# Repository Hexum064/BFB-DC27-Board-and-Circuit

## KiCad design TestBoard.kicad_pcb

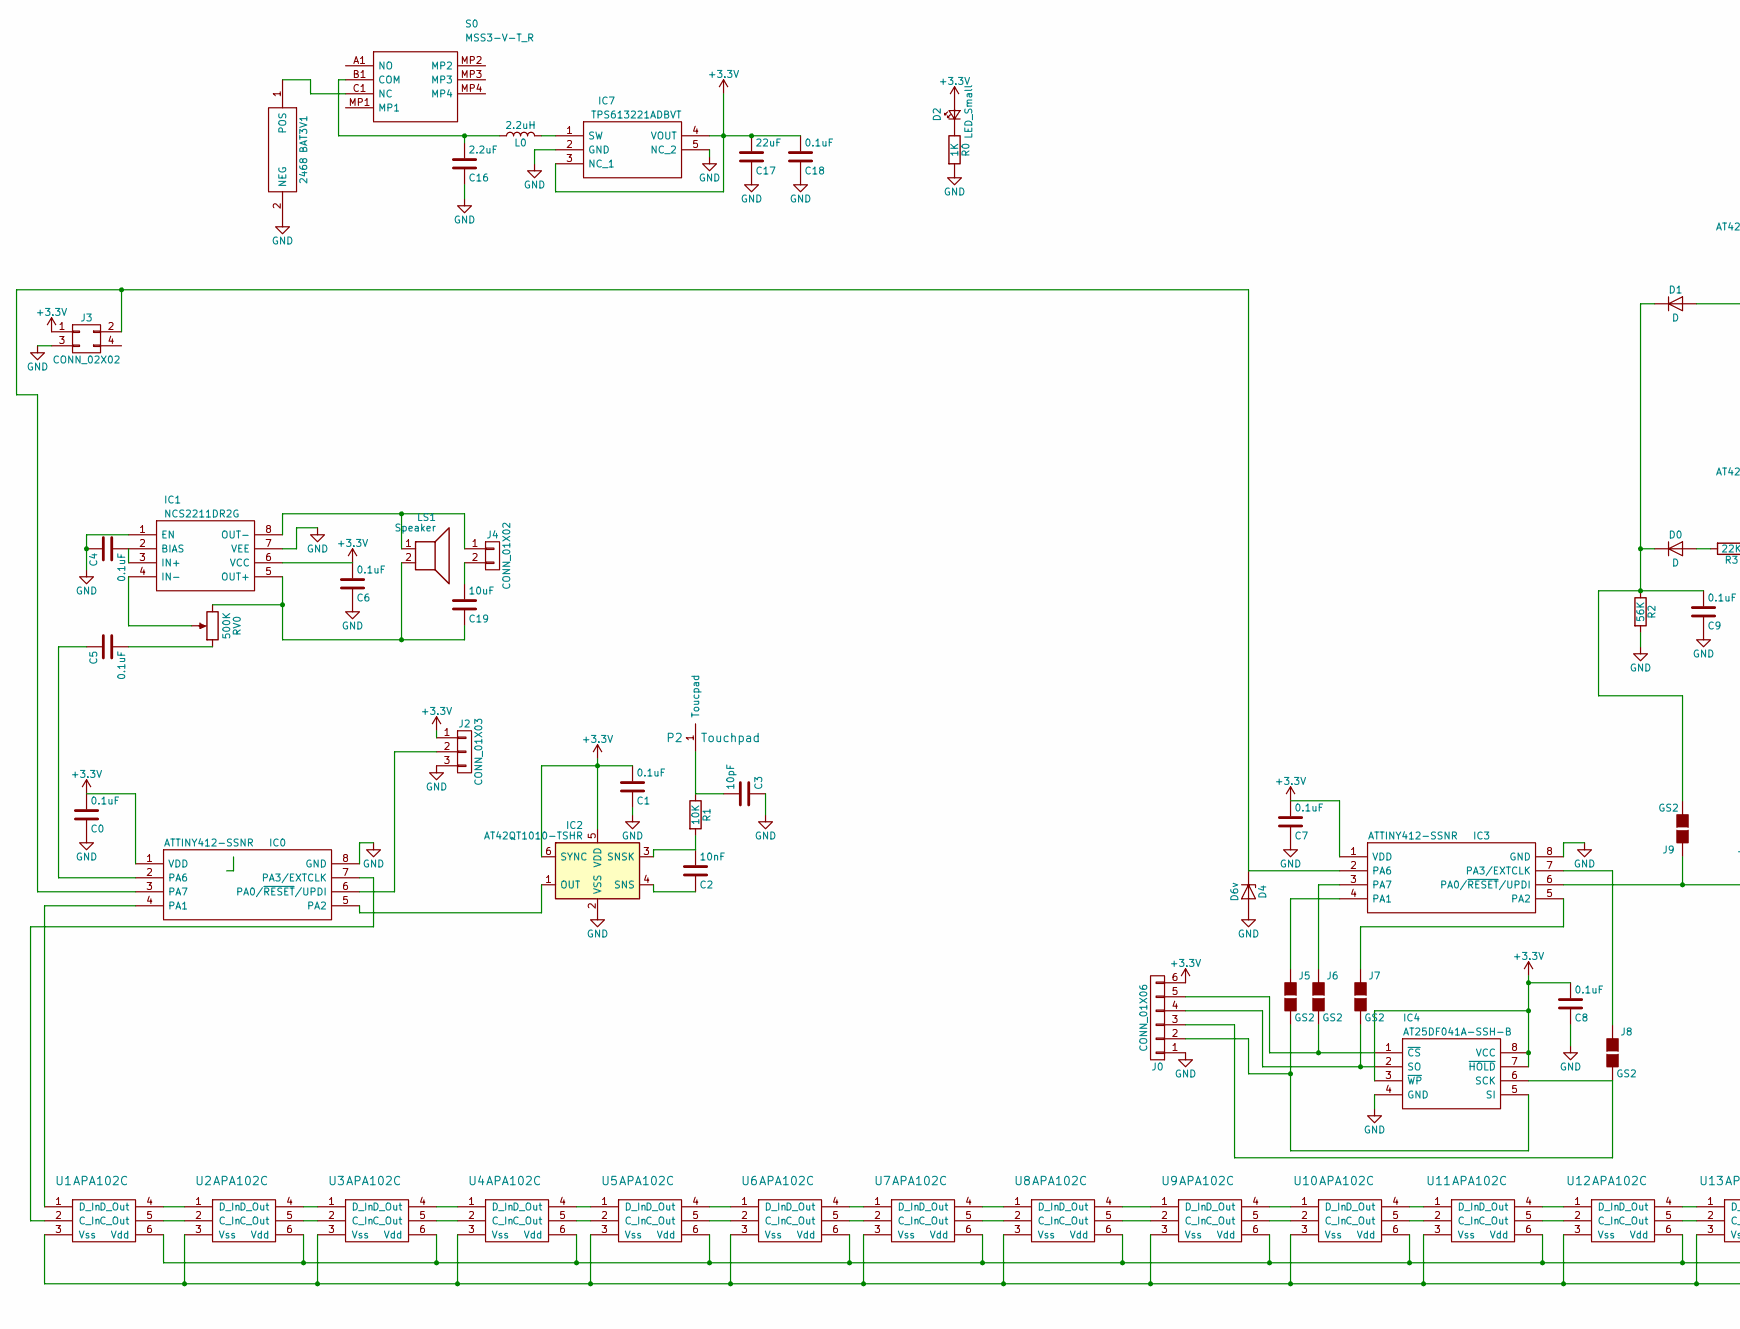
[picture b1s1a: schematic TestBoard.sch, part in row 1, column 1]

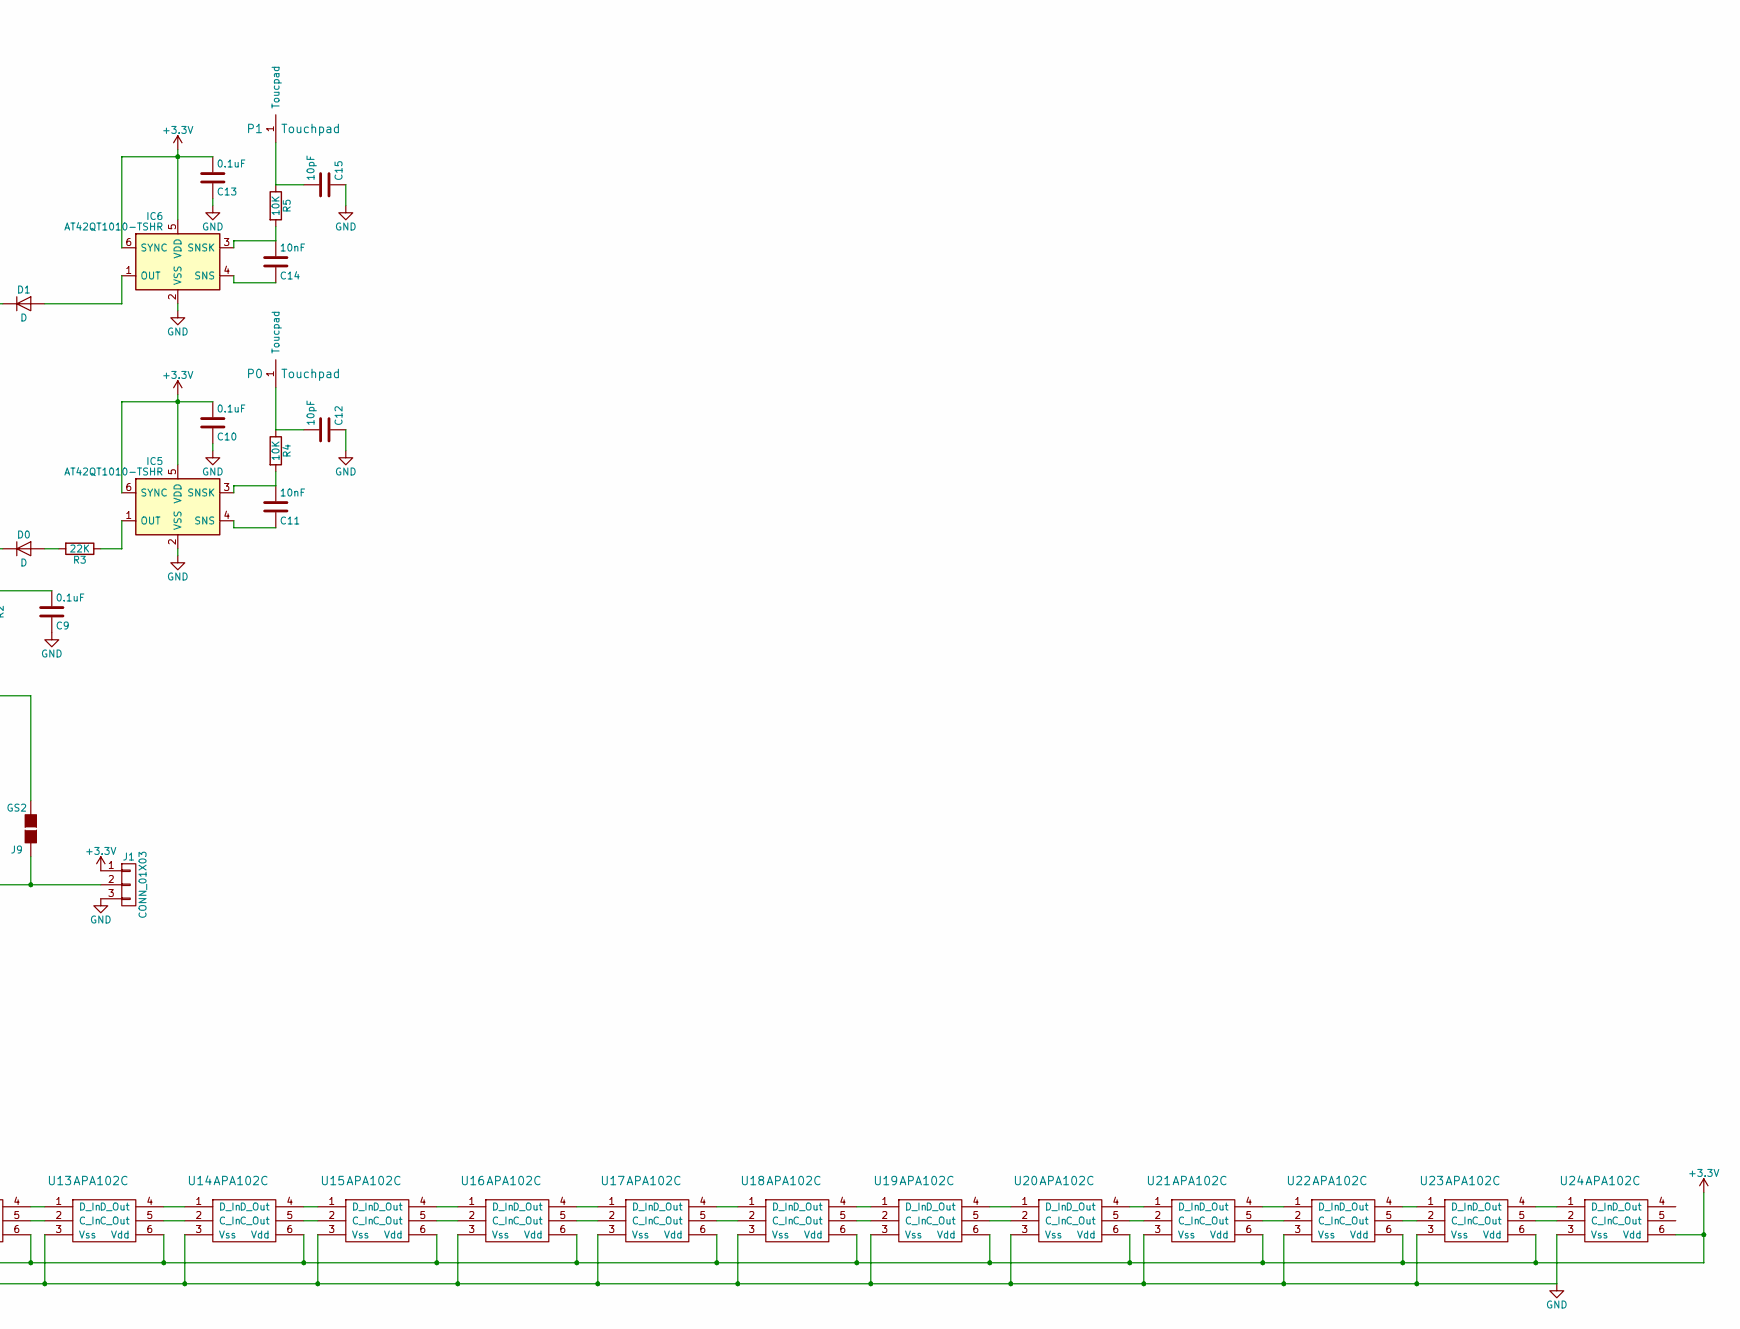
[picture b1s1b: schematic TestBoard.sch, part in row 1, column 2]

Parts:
BAT3V1: 2468; Manufacturer_Part_Number 2468; Mouser Part Number 534-2468
C0, C1, C4, C5, C6, C7, C8, C9, C10, C13, C18: 0.1uF; C_0603
C2, C11, C14: 10nF; C_0603
C3, C12, C15: 10pF; C_0603
C16: 2.2uF; C_0603
C17: 22uF; C_0603
C19: 10uF; C_0603
D0, D1: D; D_0603
D2: LED_Small; LED_0603
D4: D6v; D_0603
IC0, IC3: ATTINY412-SSNR; SOIC127P600X175-8N; Manufacturer_Part_Number ATTINY412-SSNR; Mouser Part Number 556-ATTINY412-SSNR
IC1: NCS2211DR2G; SOIC127P600X175-8N; Manufacturer_Part_Number NCS2211DR2G; Mouser Part Number 863-NCS2211DR2G
IC2, IC5, IC6: AT42QT1010-TSHR; SOT-23-6
IC4: AT25DF041A-SSH-B; SOIC127P600X175-8N; Manufacturer_Part_Number AT25DF041A-SSH-B
IC7: TPS613221ADBVT; SOT95P280X145-5N; Manufacturer_Part_Number TPS613221ADBVT; Mouser Part Number 595-TPS613221ADBVT
J0: CONN_01X06; Pin_Header_Straight_1x06_Pitch2.54mm
J1, J2: CONN_01X03; Pin_Header_Straight_1x03_Pitch2.54mm
J3: CONN_02X02; Pin_Header_Straight_2x02_Pitch2.54mm
J4: CONN_01X02; Pin_Header_Straight_1x02_Pitch2.54mm
J5, J6, J7, J8, J9: GS2
L0: 2.2uH; L_Neosid_SMS-ME3015
LS1: Speaker; Pin_Header_Straight_1x02_Pitch2.54mm
P0, P1, P2: Touchpad
R0: 1K; R_0603
R1, R4, R5: 10K; R_0603
R2: 56K; R_0603
R3: 22K; R_0603
RV0: 500K; Potentiometer_Trimmer_Vishay_TS53YJ
S0: MSS3-V-T_R; MSS3VTR; Manufacturer_Part_Number MSS3-V-T/R; Mouser Part Number 113-MSS3-V-T/R
U1, U2, U3, U4, U5, U6, U7, U8, U9, U10, U11, U12, U13, U14, U15, U16, U17, U18, U19, U20, U21, U22, U23, U24: APA102C; LED_RGB_5050-6

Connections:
+3V3: C0.2, C1.2, C6.2, C7.2, C8.2, C10.2, C13.2, C17.2, C18.2, D2.2 (A), IC0.1 (VDD), IC1.6 (VCC), IC2.5 (VDD), IC2.6 (SYNC), IC3.1 (VDD), IC4.3 (~WP), IC4.7 (~HOLD), IC4.8 (VCC), IC5.5 (VDD), IC5.6 (SYNC), IC6.5 (VDD), IC6.6 (SYNC), IC7.3 (NC_1), IC7.4 (VOUT), J0.6, J1.1, J2.1, J3.1, U1.6 (Vdd), U2.6 (Vdd), U3.6 (Vdd), U4.6 (Vdd), U5.6 (Vdd), U6.6 (Vdd), U7.6 (Vdd), U8.6 (Vdd), U9.6 (Vdd), U10.6 (Vdd), U11.6 (Vdd), U12.6 (Vdd), U13.6 (Vdd), U14.6 (Vdd), U15.6 (Vdd), U16.6 (Vdd), U17.6 (Vdd), U18.6 (Vdd), U19.6 (Vdd), U20.6 (Vdd), U21.6 (Vdd), U22.6 (Vdd), U23.6 (Vdd), U24.6 (Vdd)
GND: BAT3V1.2 (NEG), C0.1, C1.1, C3.1, C4.1, C6.1, C7.1, C8.1, C9.1, C10.1, C12.1, C13.1, C15.1, C16.1, C17.1, C18.1, D4.2 (A), IC0.8 (GND), IC1.1 (EN), IC1.7 (VEE), IC2.2 (VSS), IC3.8 (GND), IC4.4 (GND), IC5.2 (VSS), IC6.2 (VSS), IC7.2 (GND), IC7.5 (NC_2), J0.1, J1.3, J2.3, J3.3, R0.2, R2.2, U1.3 (Vss), U2.3 (Vss), U3.3 (Vss), U4.3 (Vss), U5.3 (Vss), U6.3 (Vss), U7.3 (Vss), U8.3 (Vss), U9.3 (Vss), U10.3 (Vss), U11.3 (Vss), U12.3 (Vss), U13.3 (Vss), U14.3 (Vss), U15.3 (Vss), U16.3 (Vss), U17.3 (Vss), U18.3 (Vss), U19.3 (Vss), U20.3 (Vss), U21.3 (Vss), U22.3 (Vss), U23.3 (Vss), U24.3 (Vss)
unnamed: BAT3V1.1 (POS), S0.C1 (NC)
unnamed: C2.1, IC2.4 (SNS)
unnamed: C2.2, IC2.3 (SNSK), R1.2
unnamed: C3.2, P2.1, R1.1
unnamed: C4.2, IC1.2 (BIAS), IC1.3 (IN+)
unnamed: C5.1, IC0.2 (PA6)
unnamed: C5.2, RV0.1
unnamed: C9.2, D0.1 (K), D1.1 (K), J9.2 (G2), R2.1
unnamed: C11.1, IC5.4 (SNS)
unnamed: C11.2, IC5.3 (SNSK), R4.2
unnamed: C12.2, P0.1, R4.1
unnamed: C14.1, IC6.4 (SNS)
unnamed: C14.2, IC6.3 (SNSK), R5.2
unnamed: C15.2, P1.1, R5.1
unnamed: C16.2, L0.1, S0.B1 (COM)
unnamed: C19.1, IC1.5 (OUT+), LS1.2, RV0.3
unnamed: C19.2, J4.2
unnamed: D0.2 (A), R3.2
unnamed: D1.2 (A), IC6.1 (OUT)
unnamed: D2.1 (K), R0.1
unnamed: D4.1 (K), IC0.3 (PA7), IC3.2 (PA6), J3.2
unnamed: IC0.4 (PA1), U1.1 (D_In)
unnamed: IC0.5 (PA2), IC2.1 (OUT)
unnamed: IC0.6 (PA0/~RESET~/UPDI), J2.2
unnamed: IC0.7 (PA3/EXTCLK), U1.2 (C_In)
unnamed: IC1.4 (IN-), RV0.2
unnamed: IC1.8 (OUT-), J4.1, LS1.1
unnamed: IC3.3 (PA7), J6.1 (G1)
unnamed: IC3.4 (PA1), J5.1 (G1)
unnamed: IC3.5 (PA2), J7.1 (G1)
unnamed: IC3.6 (PA0/~RESET~/UPDI), J1.2, J9.1 (G1)
unnamed: IC3.7 (PA3/EXTCLK), J8.1 (G1)
unnamed: IC4.1 (~CS), J0.5, J6.2 (G2)
unnamed: IC4.2 (SO), J0.4, J7.2 (G2)
unnamed: IC4.5 (SI), J0.2, J5.2 (G2)
unnamed: IC4.6 (SCK), J0.3, J8.2 (G2)
unnamed: IC5.1 (OUT), R3.1
unnamed: IC7.1 (SW), L0.2
unnamed: U1.4 (D_Out), U2.1 (D_In)
unnamed: U1.5 (C_Out), U2.2 (C_In)
unnamed: U2.4 (D_Out), U3.1 (D_In)
unnamed: U2.5 (C_Out), U3.2 (C_In)
unnamed: U3.4 (D_Out), U4.1 (D_In)
unnamed: U3.5 (C_Out), U4.2 (C_In)
unnamed: U4.4 (D_Out), U5.1 (D_In)
unnamed: U4.5 (C_Out), U5.2 (C_In)
unnamed: U5.4 (D_Out), U6.1 (D_In)
unnamed: U5.5 (C_Out), U6.2 (C_In)
unnamed: U6.4 (D_Out), U7.1 (D_In)
unnamed: U6.5 (C_Out), U7.2 (C_In)
unnamed: U7.4 (D_Out), U8.1 (D_In)
unnamed: U7.5 (C_Out), U8.2 (C_In)
unnamed: U8.4 (D_Out), U9.1 (D_In)
unnamed: U8.5 (C_Out), U9.2 (C_In)
unnamed: U9.4 (D_Out), U10.1 (D_In)
unnamed: U9.5 (C_Out), U10.2 (C_In)
unnamed: U10.4 (D_Out), U11.1 (D_In)
unnamed: U10.5 (C_Out), U11.2 (C_In)
unnamed: U11.4 (D_Out), U12.1 (D_In)
unnamed: U11.5 (C_Out), U12.2 (C_In)
unnamed: U12.4 (D_Out), U13.1 (D_In)
unnamed: U12.5 (C_Out), U13.2 (C_In)
unnamed: U13.4 (D_Out), U14.1 (D_In)
unnamed: U13.5 (C_Out), U14.2 (C_In)
unnamed: U14.4 (D_Out), U15.1 (D_In)
unnamed: U14.5 (C_Out), U15.2 (C_In)
unnamed: U15.4 (D_Out), U16.1 (D_In)
unnamed: U15.5 (C_Out), U16.2 (C_In)
unnamed: U16.4 (D_Out), U17.1 (D_In)
unnamed: U16.5 (C_Out), U17.2 (C_In)
unnamed: U17.4 (D_Out), U18.1 (D_In)
unnamed: U17.5 (C_Out), U18.2 (C_In)
unnamed: U18.4 (D_Out), U19.1 (D_In)
unnamed: U18.5 (C_Out), U19.2 (C_In)
unnamed: U19.4 (D_Out), U20.1 (D_In)
unnamed: U19.5 (C_Out), U20.2 (C_In)
unnamed: U20.4 (D_Out), U21.1 (D_In)
unnamed: U20.5 (C_Out), U21.2 (C_In)
unnamed: U21.4 (D_Out), U22.1 (D_In)
unnamed: U21.5 (C_Out), U22.2 (C_In)
unnamed: U22.4 (D_Out), U23.1 (D_In)
unnamed: U22.5 (C_Out), U23.2 (C_In)
unnamed: U23.4 (D_Out), U24.1 (D_In)
unnamed: U23.5 (C_Out), U24.2 (C_In)

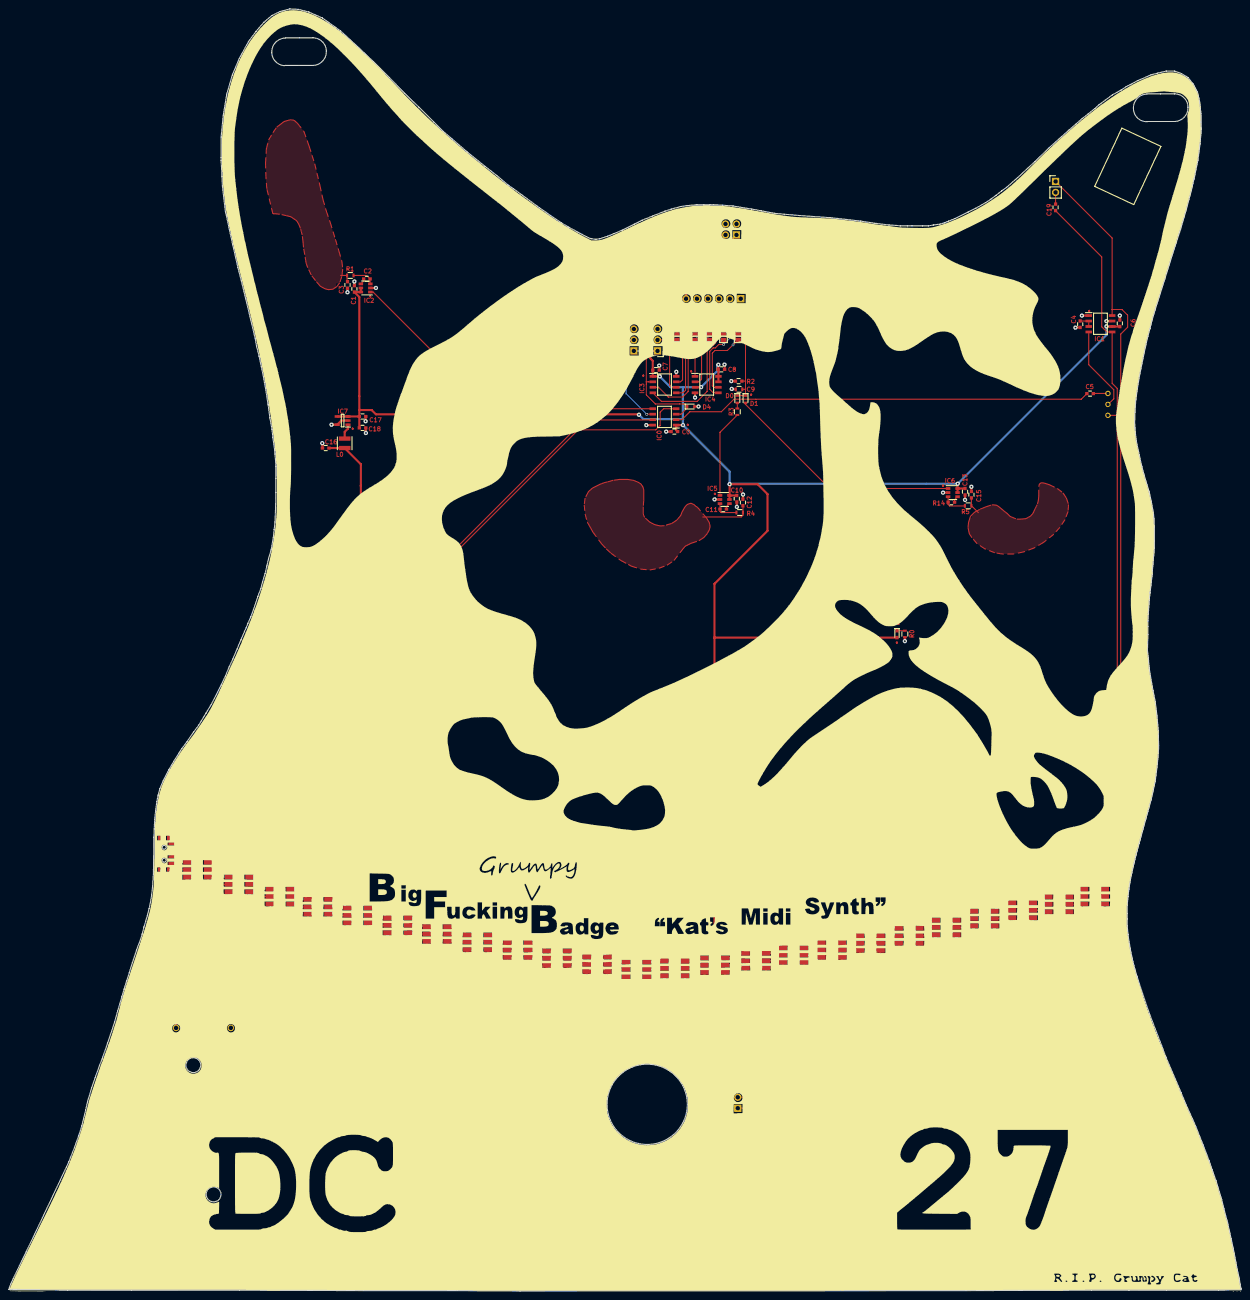
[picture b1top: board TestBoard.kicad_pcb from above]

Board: 2 copper layers, 285.7 x 297.3 mm, 77 parts (1 on the bottom side), 86 nets.

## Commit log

2019-07-26 Board and Schematic
2019-07-26 Added parts
